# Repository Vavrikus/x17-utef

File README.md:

# X17 TPC simulation and reconstruction
C++ code in this project uses ROOT and Garfield++ to simulate and reconstruct electron and positron tracks inside the atypic TPC of the X17 project. The workflow is split between several scripts.

## Installation
The user needs to have ROOT installed (built on 6.26/06), for running simulations Garfield++ has to be installed. Currently used simulation results are provided.
Scripts have to be compiled before running:

```bash
cd /path/to/project/folder
mkdir build && cd build
cmake ..
make
./script_name
```

Alternatively, the script *rebuild_debug.sh* or *rebuild_release.sh* can be used. All of the binaries will be saved to the newly made build folder. This might lead to errors in the scripts whenever relative paths are used.

### Map simulation
The map of the ionization electron drift can be simulated on MetaCentrum:
1. Files need to be synchronized and compiled (can be achieved by adjusting *sync.sh* and *remote_compile.sh*).
2. Directory *data/ion_map/new_sample* should be cleared so no files get overwritten.
3. Simulation is started by executing *ion_multiple.sh*:

    ```bash
    ./ion_multiple.sh num_of_threads step_size_cm num_of_iterations_per_electron
    ```
    Make sure wall time and memory inside *ion_single.sh* are sufficient.
4. After the job finishes, output files ion(id).root and ion(id).out are sent into the data directory. You can fetch them by adjusting *fetch_data.sh*.
5. Map can be compiled using script *make_map.cpp* (ion.root files have to be in the data directory).

### Microscopic track simulation
Microscopic tracks can be simulated on MetaCentrum:
1. Files need to be synchronized and compiled (can be achieved by adjusting *sync.sh* and *remote_compile.sh*).
2. Directory *data/micro_tracks/new_tracks* should be cleared so no files get overwritten.
3. Simulation is started by executing *track_multi.sh*:

    ```bash
    ./track_multi.sh num_of_threads num_of_iterations_per_track num_of_angle_bins num_of_energy_bins
    ```
    If only *num_of_threads* parameter is provided the track parameters will be random instead of grid-like. Make sure wall time and memory inside *track_single.sh* are sufficient.
4. After the job finishes, output files track_full(id).root, track_small(id).root and tracks(id).out are sent into the data directory. You can fetch them by adjusting *fetch_data.sh*.
5. The tracks can be reconstructed with the reco_track script.

## Usage
The project uses the following folder structure:
- **The project folder**
    - **.vscode**
        - *root-on-vscode.code-workspace* and *launch.json* -- useful setup for using ROOT and Garfield++ in Visual Studio Code with Intellisense and debuging tool (include paths need to be adjusted)
    - **tests/magnetic_field_plot**
        - *bfield.C* -- old script for displaying the magnetic field using Garfield++
    - **data**
        - **elmag**
            - Contains files *VecB.txt* and *VecE.txt* with magnetic field simulation (electric field is homogeneous) and files *VecB2.txt* and *VecE2.txt* containing the same data with adjusted coordinates.
        - **ion_map**
            - Contains files with ionization electron data and compiled map in the file *map.root*
            - *sample_1.0* contains the old map with 90/10 gas composition
            - *sample_2.0* contains the new map with 70/30 gas composition
        - **micro_tracks**
            - Contains files with microscopic track simulations (many tracks)
            - *plot_drift.C* -- ROOT script for driftline plots used in the RD51 presentation
            - Currently used tracks are in *grid_01* and *grid_02*
        - **single_track**
            - Contains files with single simulated track for different settings
            - *original*, *original_v2*, *originalMC*, *track1* are tracks with 8 MeV momentum and use old coordinates
            - *new_9010*, *new_7030* are tracks with 8 MeV momentum and use new coordinates; the latter is the only track in this group with non-0.1 eV starting ionization electron energies
            - *newest_7030* is a track with 10 MeV (?) momentum and uses new coordinates and struct MicroPoint
    - **figures**
        - Contains the newest figures (post-thesis, to be used in the article, etc.)
    - **include**
        - Contains headers for the project with doxygen comments (and .inl files with definitions of templated functions)
    - **presentations**
        - Contains presentation from meetings and seminars (tex and pdf files)
    - **reconstruction**
        - *map_test.cpp* -- script for plots of the map reconstruction residues of microscopic tracks
        - *reco_mtracks.cpp* -- script for reconstruction of microscopic tracks
        - *reco_plots.cpp* -- script for plots of the reconstruction (comparison of simulated and reconstructed energy)
        - *reco_test.cpp* -- script for reconstruction testing (single track plots, Runge-Kutta tracks circle fit)
    - **remote**
        - Useful scripts for MetaCentrum (uses absolute paths, needs to be adjusted)
        - *sync.sh* -- Syncing with MetaCentrum
        - *clear_data.sh* -- Clearing the data directories on MetaCentrum
        - *fetch_data.sh* -- Syncing data simulated on MetaCentrum
        - *remote_compile.sh* -- Compiling scripts on MetaCentrum
    - **schematics**
        - *circle_fit2d.ggb* -- GeoGebra file with 2D circle fit geometry
        - *circle_lines.ggb* -- GeoGebra file with 3D circle fit geometry
        - *GEMReadout_CenteredConector.kicad_pcb* -- KiCad file with the readout PCB
        - *map_visualization.ggb* -- Simple visualization of the map and its inverse
        - *phi_systematic_error.ggb* -- Visualization of the phi of the maxima and minima of systematic error in reconstructed energy (pads shown)
        - *tpc_layout.ggb* -- GeoGebra file with a top-down view of the TPCs (area of the first map simulation and of the magnetic field simulation shown)
        - *tpc_micro_simulation* -- Visualization of the 3D layout of the microscopic track simulation
    - **simulations**
        - **ion_map**
            - *ion_electrons.cpp* -- script for ionization electrons simulation (creates input for *make_map.cpp*)
            - *make_map.cpp* -- script for creating the map of ionization electron drift
            - *ion_multi.sh*, *ion_single.sh* -- scripts handling the map simulation on MetaCentrum (see above)
        - **rk_tracks**
            - *rk_tracks.cpp* -- script for quick Runge-Kutta track simulation, generates rk_tracks.root file (currently 100,000 tracks)
        - **single_track**
            - *gas_table.cpp* -- script for generating the gas table for AvalancheMC simulation (not necessary for microscopic tracking)
            - *make_track.cpp* -- script for single track simulation
        - **micro_tracks**
            - *micro_tracks.cpp* -- script for random or grid-like simulation of multiple microscopic tracks
            - *track_multi.sh*, *track_single.sh* -- scripts handling the simulation on MetaCentrum
        - **mcs_track** 
            - *mcs_tracks.cpp* -- Multiple Coulomb Scattering
    - **source**
        - Contains all .cpp files common to the reconstruction and simulation scripts.
    - **thesis**
        - Contains the latex and pdf files of my bachelor thesis

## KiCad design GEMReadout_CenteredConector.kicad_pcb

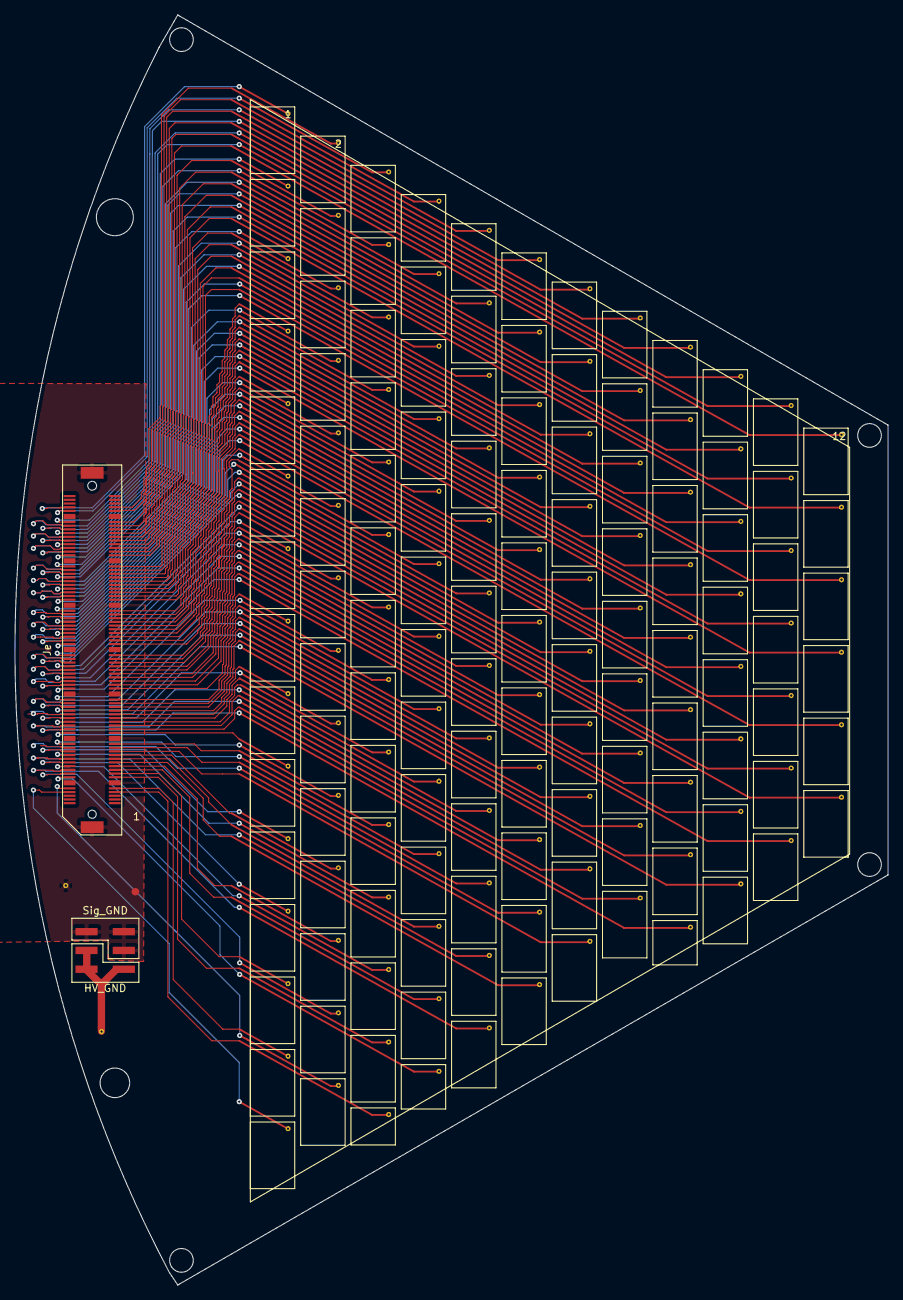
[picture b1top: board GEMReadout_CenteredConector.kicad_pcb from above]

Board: 2 copper layers, 118.0 x 171.7 mm, 3 parts (1 on the bottom side), 130 nets.

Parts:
J1: Conn_02x03_Top_Bottom; PinSocket_2x03_P2.54mm_Vertical_SMD
Je: Conn_02x70_Top_Bottom_Shielded; HRS_FX10A-140S_Receptacle_Detector
U1: Conn_02x64_PradsTrapezoid; Pads_trapezoid

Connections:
/SAMPA1_CH0: Je.19, U1.97
/SAMPA1_CH1: Je.89, U1.98
/SAMPA1_CH2: Je.18, U1.99
/SAMPA1_CH3: Je.88, U1.100
/SAMPA1_CH4: Je.17, U1.101
/SAMPA1_CH5: Je.87, U1.102
/SAMPA1_CH6: Je.16, U1.103
/SAMPA1_CH7: Je.86, U1.104
/SAMPA1_CH8: Je.15, U1.105
/SAMPA1_CH9: Je.85, U1.106
/SAMPA1_CH10: Je.14, U1.107
/SAMPA1_CH11: Je.84, U1.108
/SAMPA1_CH12: Je.13, U1.109
/SAMPA1_CH13: Je.83, U1.110
/SAMPA1_CH14: Je.12, U1.111
/SAMPA1_CH15: Je.82, U1.112
/SAMPA1_CH16: Je.11, U1.113
/SAMPA1_CH17: Je.81, U1.114
/SAMPA1_CH18: Je.10, U1.115
/SAMPA1_CH19: Je.80, U1.116
/SAMPA1_CH20: Je.9, U1.117
/SAMPA1_CH21: Je.79, U1.118
/SAMPA1_CH22: Je.8, U1.119
/SAMPA1_CH23: Je.78, U1.120
/SAMPA1_CH24: Je.7, U1.121
/SAMPA1_CH25: Je.77, U1.122
/SAMPA1_CH26: Je.6, U1.123
/SAMPA1_CH27: Je.76, U1.124
/SAMPA1_CH28: Je.5, U1.125
/SAMPA1_CH29: Je.75, U1.126
/SAMPA1_CH30: Je.4, U1.127
/SAMPA1_CH31: Je.74, U1.128
/SAMPA2_CH0: Je.20, U1.96
/SAMPA2_CH1: Je.90, U1.95
/SAMPA2_CH2: Je.21, U1.94
/SAMPA2_CH3: Je.91, U1.93
/SAMPA2_CH4: Je.22, U1.92
/SAMPA2_CH5: Je.92, U1.91
/SAMPA2_CH6: Je.23, U1.90
/SAMPA2_CH7: Je.93, U1.89
/SAMPA2_CH8: Je.24, U1.88
/SAMPA2_CH9: Je.94, U1.87
/SAMPA2_CH10: Je.25, U1.86
/SAMPA2_CH11: Je.95, U1.85
/SAMPA2_CH12: Je.26, U1.84
/SAMPA2_CH13: Je.96, U1.83
/SAMPA2_CH14: Je.27, U1.82
/SAMPA2_CH15: Je.97, U1.81
/SAMPA2_CH16: Je.28, U1.80
/SAMPA2_CH17: Je.98, U1.79
/SAMPA2_CH18: Je.29, U1.78
/SAMPA2_CH19: Je.99, U1.77
/SAMPA2_CH20: Je.30, U1.76
/SAMPA2_CH21: Je.100, U1.75
/SAMPA2_CH22: Je.31, U1.74
/SAMPA2_CH23: Je.101, U1.73
/SAMPA2_CH24: Je.32, U1.72
/SAMPA2_CH25: Je.102, U1.71
/SAMPA2_CH26: Je.33, U1.70
/SAMPA2_CH27: Je.103, U1.69
/SAMPA2_CH28: Je.34, U1.68
/SAMPA2_CH29: Je.104, U1.67
/SAMPA2_CH30: Je.35, U1.66
/SAMPA2_CH31: Je.105, U1.65
/SAMPA3_CH0: Je.51, U1.33
/SAMPA3_CH1: Je.121, U1.34
/SAMPA3_CH2: Je.50, U1.35
/SAMPA3_CH3: Je.120, U1.36
/SAMPA3_CH4: Je.49, U1.37
/SAMPA3_CH5: Je.119, U1.38
/SAMPA3_CH6: Je.48, U1.39
/SAMPA3_CH7: Je.118, U1.40
/SAMPA3_CH8: Je.47, U1.41
/SAMPA3_CH9: Je.117, U1.42
/SAMPA3_CH10: Je.46, U1.43
/SAMPA3_CH11: Je.116, U1.44
/SAMPA3_CH12: Je.45, U1.45
/SAMPA3_CH13: Je.115, U1.46
/SAMPA3_CH14: Je.44, U1.47
/SAMPA3_CH15: Je.114, U1.48
/SAMPA3_CH16: Je.43, U1.49
/SAMPA3_CH17: Je.113, U1.50
/SAMPA3_CH18: Je.42, U1.51
/SAMPA3_CH19: Je.112, U1.52
/SAMPA3_CH20: Je.41, U1.53
/SAMPA3_CH21: Je.111, U1.54
/SAMPA3_CH22: Je.40, U1.55
/SAMPA3_CH23: Je.110, U1.56
/SAMPA3_CH24: Je.39, U1.57
/SAMPA3_CH25: Je.109, U1.58
/SAMPA3_CH26: Je.38, U1.59
/SAMPA3_CH27: Je.108, U1.60
/SAMPA3_CH28: Je.37, U1.61
/SAMPA3_CH29: Je.107, U1.62
/SAMPA3_CH30: Je.36, U1.63
/SAMPA3_CH31: Je.106, U1.64
/SAMPA4_CH0: Je.52, U1.32
/SAMPA4_CH1: Je.122, U1.31
/SAMPA4_CH2: Je.53, U1.30
/SAMPA4_CH3: Je.123, U1.29
/SAMPA4_CH4: Je.54, U1.28
/SAMPA4_CH5: Je.124, U1.27
/SAMPA4_CH6: Je.55, U1.26
/SAMPA4_CH7: Je.125, U1.25
/SAMPA4_CH8: Je.56, U1.24
/SAMPA4_CH9: Je.126, U1.23
/SAMPA4_CH10: Je.57, U1.22
/SAMPA4_CH11: Je.127, U1.21
/SAMPA4_CH12: Je.58, U1.20
/SAMPA4_CH13: Je.128, U1.19
/SAMPA4_CH14: Je.59, U1.18
/SAMPA4_CH15: Je.129, U1.17
/SAMPA4_CH16: Je.60, U1.16
/SAMPA4_CH17: Je.130, U1.15
/SAMPA4_CH18: Je.61, U1.14
/SAMPA4_CH19: Je.131, U1.13
/SAMPA4_CH20: Je.62, U1.12
/SAMPA4_CH21: Je.132, U1.11
/SAMPA4_CH22: Je.63, U1.10
/SAMPA4_CH23: Je.133, U1.9
/SAMPA4_CH24: Je.64, U1.8
/SAMPA4_CH25: Je.134, U1.7
/SAMPA4_CH26: Je.65, U1.6
/SAMPA4_CH27: Je.135, U1.5
/SAMPA4_CH28: Je.66, U1.4
/SAMPA4_CH29: Je.136, U1.3
/SAMPA4_CH30: Je.67, U1.2
/SAMPA4_CH31: Je.137, U1.1
GND: J1.1, J1.2, J1.4, Je.SH
GNDPWR: J1.3, J1.5, J1.6

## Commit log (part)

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2022-08-23 Initialized git.
2022-08-23 Added vscode workspace.
2022-08-24 Saving ionization electron data to root file.
2022-08-24 First track reconstruction prototype using yt-relation.
2022-08-25 Plotting residues of reconstructed track.
2022-08-25 Loading and interpolating magnetic field from txt file.
2022-08-26 Using round instead of floor (bug fix).
2022-08-29 Energy reconstruction, first working prototype.
2022-08-30 Energy reconstruction using circle and lines fit.
2022-08-30 Simulating stationary electrons in the entire volume of detector.
2022-10-03 Adjusted ion simulation for metacentum, unresolved bugs.
2022-10-07 Adjusted paths to new folder structure.
2022-10-07 Warnings reduced: not sourcing root when running interactively.
2022-10-07 Fixed compiling and qsub issues.
2022-10-07 Better output, bug fixes.
2022-10-07 Added script for fetching data from metacentrum.
2022-10-10 Better distribution of works between individual jobs.
2022-10-10 Added parameter for generating more electrons in each simulated point.
2022-10-10 Bug fixes.
2022-10-14 Added make_map for processing data and outputing averages into field.
2022-10-17 Checking if field index is out of bounds.
2022-10-17 Track reconstruction from map, first untuned prototype.
2022-10-17 Fixed bug (now saving averages as supposed to).
2022-10-27 Drawing ionization electrons displacement with arrows.
2022-10-27 Added yz,zt and yt plots.
2022-10-31 Plotting with errorbars.
2022-11-11 Changed z1:t1 to z0:t1, added xz:t1, xz track plot.
2022-11-18 Added X17Utilities for X17 specific functions and variables. Small improvements of Vector struct.
2022-11-21 Generating gas table, AvalancheMC simulation.
2022-11-28 Added pads coordinates and function for getting their corners.
2022-11-28 Code improvement GetPadCorners.
2022-12-05 Added doxygen comments.
2022-12-09 Trying to implement interpolation in the inverse grid.
2023-02-24 First working prototype of interpolation in the inverse grid, drawing distorted pads.
2023-02-24 Fixed TPC dimension error.
2023-02-24 Added tpc_layout GeoGebra file.
2023-03-02 Changed coordinate system (x,y,z) --> (y,z,x). Distorted pads working ok, some files may now contain bugs.
2023-03-03 Changed coordinates in magnetic and electric field text files.
2023-03-09 Minor code adjustments, added presentation from 07-03-2023 seminar.
2023-03-09 Drawing residuals of reconstruction.
2023-03-09 Minor bug fixes.
2023-03-09 Fixed pad coordinates, added nogaps option, GetPadCenter function.
2023-03-10 Reconstructing binned points.
2023-03-16 Added GeoGebra file with circle fit geometry.
2023-03-17 First attempt at 3D circle and lines fit (bugs).
2023-03-23 Added README, added root files from different simulations, no more copies of mag_data.
2023-03-23 Fixed bugs in 3D fit and energy calculation.
2023-03-23 Drawing binned reconstruction with TMarkerBox3D, drawing energy along track.
2023-03-29 Implemented Runge-Kutta numerical integration.
2023-03-30 Implemented Runge-Kutta fit.
2023-03-30 Improved track reconstruction drawing.
2023-03-31 Rewritten reco_track using new classes TrackLoop and Task.
2023-03-31 Added Runge-Kutta tracks generation.
2023-03-31 Fitting with circle only doesn't work well, added as comment.
2023-04-06 Comparing RK simulated energy to circle fit energy.
2023-04-06 Tuned circle fitting.
2023-04-06 Plotting energy sigma at different energies.
2023-04-11 Changing folder structure step 1: Moving files to new folders.
2023-04-11 Changing folder structure step 2: Added new data files, updated gitignore.
2023-04-11 Changing folder structure step 3: Changed paths inside the code.
2023-04-11 Changing folder structure step 4: Updated CMakeLists.
2023-04-12 Drawing energy difference histograms.
2023-05-05 Added presentation from 28-04-23 meeting.
2023-05-05 Temporary correlation addition (will be reworked).
2023-05-05 Major code changes (data structures, organization, minor optimization).
2023-05-05 Fixed some bugs in redesigned code.
2023-05-05 Saving C++ default types instead of custom class.
2023-05-05 Split headers into .h and .cpp files.
2023-05-12 Fixed bugs. File ion_electron.cpp now compiles.
2023-05-12 Single track microscopic simulation compilation OK.
2023-05-12 File reco_track.cpp will now be compiled, compilation OK.
2023-05-12 Magnetic field in centimeters just as any other Field object (map).
2023-05-12 Fixed more bugs, make_map.cpp will now be compiled, compilation OK.
2023-05-12 Improved formatting.
2023-05-14 Improved 'const' keyword usage.
2023-05-14 Formatting improvements.
2023-05-14 Updated README.
2023-05-14 Fixed anode position in IsInSector function.
2023-05-14 Fixed minor bugs.
2023-05-16 Updated first sector condition, changed gas composition.
2023-05-16 Updated scripts for running on MetaCentrum.
2023-05-17 Fixed problems with running on MetaCentrum.
2023-05-17 Resolved annoying version info errors.
2023-05-18 Fixed map simulation settings, updated walltime to 48h.
2023-05-18 Updated VS Code configuration for debugging.
2023-05-18 Using getters instead of weird approach with references (bug fix).
2023-05-19 Fixed make_map, now using ROOT dictionary to save the map.
2023-05-19 Fixed rk_tracks.
2023-05-25 Added 70/30 map simulation, adjusted make_map.
2023-06-06 Updated single track microscopic simulation to 70/30 composition.
2023-06-06 Updated reconstruction to 70/30 single microscopic track.
2023-06-07 Added the skeleton of thesis.
2023-06-13 Added summaries to several sections, figures.
2023-06-14 Added track reconstruction summary.
2023-06-16 Minor changes based on provided notes.
2023-06-16 Using MFF UK standards.
2023-10-05 Adjusted scripts for microscopic track simulation.
2023-10-11 Trying to run micro_tracks on MetaCentrum (unsuccessful, maybe ROOT reinstall needed).
2023-10-11 Added an option of grid-like simulation.
2023-10-18 Fixed Run(true) issue and bad sensor settings.
2023-10-20 Added random track simulation No. 1.
2023-10-24 Added drift line storing.
2023-10-24 Tested correct track parameter generation for grid-like simulation.
2023-10-25 Added saving with and without driftlines.
2023-10-25 No more testing on 1 electron.
2023-10-26 Tested double file simulation of tracks, few minor adjustments.
2023-11-02 Added first somewhat successful grid-like simulation results.
2023-11-03 First successful reconstruction of one of the new microscopic tracks.
2023-11-03 Adjusted reconstruction for multiple (5) tracks.
2023-11-03 Fixed circle fit ranges, cutting failed electrons (not propagated all the way).
2023-11-07 Reconstructing tracks from multiple files (not 100 % functional).
2023-11-08 Fixed issue in RKFit exit condition.
2023-11-08 First complete reconstruction of 4172 tracks.
2023-11-08 Better axes in the tracks_fit plot.
2023-11-08 Added cca month old map visualization.
2023-11-09 Fixed an off-by-one error in track parameter generation.
2023-11-09 Saving the reconstruction results.
2023-11-09 Added new script for plotting reconstruction results.
2023-11-09 Added newest grid-like simulation results (almost complete).
2023-11-09 Added extra plots, fixed binning (no empty bins from rounding errors).
2023-11-10 Improved plotting (using canvases).
2023-11-10 Added theta and phi plots, added presentation for 10-11-23 meeting.
2023-11-14 Organized presentations into separate folders.
2023-11-14 Started using list of abbreviations.
2023-11-15 Ignoring unnecessary latex output.
2023-11-15 Removed remnants of old files.
2023-11-16 Added the rest of new grid01 simulations.
2023-11-16 Added microscopic simulation with multiple iterations, fixed possible rounding errors.
2023-11-22 Added first version of the RD51 presentation.
2023-11-28 Third version of the RD51 presentation (mostly completed until slide 14/20).
2023-11-30 Added fourth version of the RD51 presentation (almost final).
2023-12-05 Final (?) version of the RD51 presentation.
2023-12-14 Added new simulations of 4*9702 tracks.
2023-12-14 Added reconstruction results with the new simulation data + presentation.
2024-03-02 Addressed 7/151 commits in the thesis.
2024-03-05 Addressed 8/151 commits in the thesis.
2024-03-08 Addressed 10/151 commits in the thesis.
2024-03-25 Addressed 19/151 commits in the thesis.
2024-10-11 Grammatical and stylistic improvements.
2024-10-14 Addressed 24/151 commits in the thesis.
2024-10-20 Adjusted workspace: using include paths instead of extra workspace folders.
2024-10-29 Addressed 32/151 commits in the thesis.
2024-10-31 Addressed 36/151 commits in the thesis.
2024-11-08 Fixed a bug in the z-coordinate inverse map binary search.
2024-11-08 Addressed 46/151 commits in the thesis.
2024-11-19 Addressed most of the comments.
2024-11-30 Added ATOMKI measurement description.
2025-03-07 Adjustments to the ATOMKI anomaly section, theoretical explanations, short outline of the X17 at CTU.
2025-03-13 Other experiments section of ATOMKI anomaly.
2025-03-13 X17 at IEAP CTU section.
2025-03-17 Added general part about TPC.
2025-03-24 Magnetic field plots, pads plot.
2025-03-25 Addressed 48/151 commits in the thesis.
2025-03-26 Fixed integer/double bug in trilinear interpolation.
2025-03-31 Addressed the notes + few improvements.
2025-03-31 Addressed 54/151 commits in the thesis.
2025-04-01 Fixed the magnetic field plots (volume outlines), magnet coordinates still off.
2025-04-07 Addressed 55/151 commits in the thesis.
2025-04-09 Addressed 56/151 commits in the thesis -- Runge-Kutta fit draft.
2025-04-12 Updated to BibLaTeX/Biber + jabbrv.
2025-04-24 Addressed 151/151 commits in the thesis, moving on to the figures.
2025-04-30 Added old track files.
2025-04-30 Plotting old 90:10 and 70:30 drift lines.
2025-04-30 Plotting Runge-Kutta comparison with HEED.
2025-05-03 Added reconstruction assuming steady drift figures.
2025-05-12 Calculating the map covariance matrix + bottom layer plot, Mahalanobis dist. QQ plot.
2025-05-15 Implemented Mardia's test.
2025-05-22 Added new map distortion plots + thesis.
2025-05-28 Chapter 1 improved structure, some additions (Examples not complete).
2025-06-02 Chapter 4 fixes, 3D circle and RK4 fit figures.
2025-06-03 Added TPC examples to chapter 1.
2025-06-30 Added map inversion reconstruction figures.
2025-07-10 Added 2D circle fit and spline fit plots, preparing pad plots.
2025-07-11 Added pad 12 and 66 reconstruction plots, part of the conclusion.
2025-07-12 Track reconstruction with pads example.
2025-07-15 Added circle fit of runge kutta tracks.
2025-07-16 Part of the conclusion, abstract.
2025-07-16 Switching to newer MFF UK template built with latexmk, resolved PDF/A issue (\texttildelow).
2025-07-16 Plotting Runge-Kutta fit of grid sample result.
2025-07-16 Added remaining figures and their description.
2025-07-16 Conclusion and Czech abstract.
2025-07-17 Addressed notes, removed less relevant ones.
2025-07-17 Addressed more notes, small fixes.
2025-07-17 Final tweaks, dedication, only grammar check to go.
2025-07-17 Final version of the thesis. Not all grammar was checked in the end.
2025-07-18 Abstract output (if needed later).
2025-07-20 Split Points.h into multiple files.
2025-07-21 Testing map residuals on all tracks. Correction of systematic errors in reconstructed energy with 3D linear fit.
2025-07-30 Plot improvements.
2025-10-17 Added thesis defense presentation and DRD1 Warsaw poster.
2025-11-21 Added new driftline figures (restricted to the OFTPC volume).
2025-11-21 Added pdf figures (tracks fit in OFTPC, extra bin, label size).
2025-11-28 Removed excessive code duplication.
2025-12-04 Implemented skewed Gauss (not used in the end), excessive code duplication removed.
2025-12-18 Improved pad inversion plots.
2025-12-18 Added improved map residual plots.
2025-12-18 Added taks for comparison of old and new map inversion.
2025-12-18 Improved cview_update to make changing canvas possible (using Gemini).
2025-12-20 Added pdf reconstruction result figures, correct labels.
2026-02-23 Added pad distribution plotting.
2026-02-24 First version of 7th DRD1 meeting presentation.
2026-03-04 Final version of DRD1 7th meeting presentation.
2026-03-13 Updated scripts for MetaCentrum (but they can cause UID issues with jobs).
